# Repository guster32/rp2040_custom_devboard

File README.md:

https://datasheets.raspberrypi.com/rp2040/rp2040-datasheet.pdf

https://cdn.sparkfun.com/assets/5/d/3/1/f/hardware-design-with-rp2040.pdf

https://datasheets.raspberrypi.com/rp2040/MinimalKiCAD.zip

https://github.com/sethhillbrand/kicad_templates.git

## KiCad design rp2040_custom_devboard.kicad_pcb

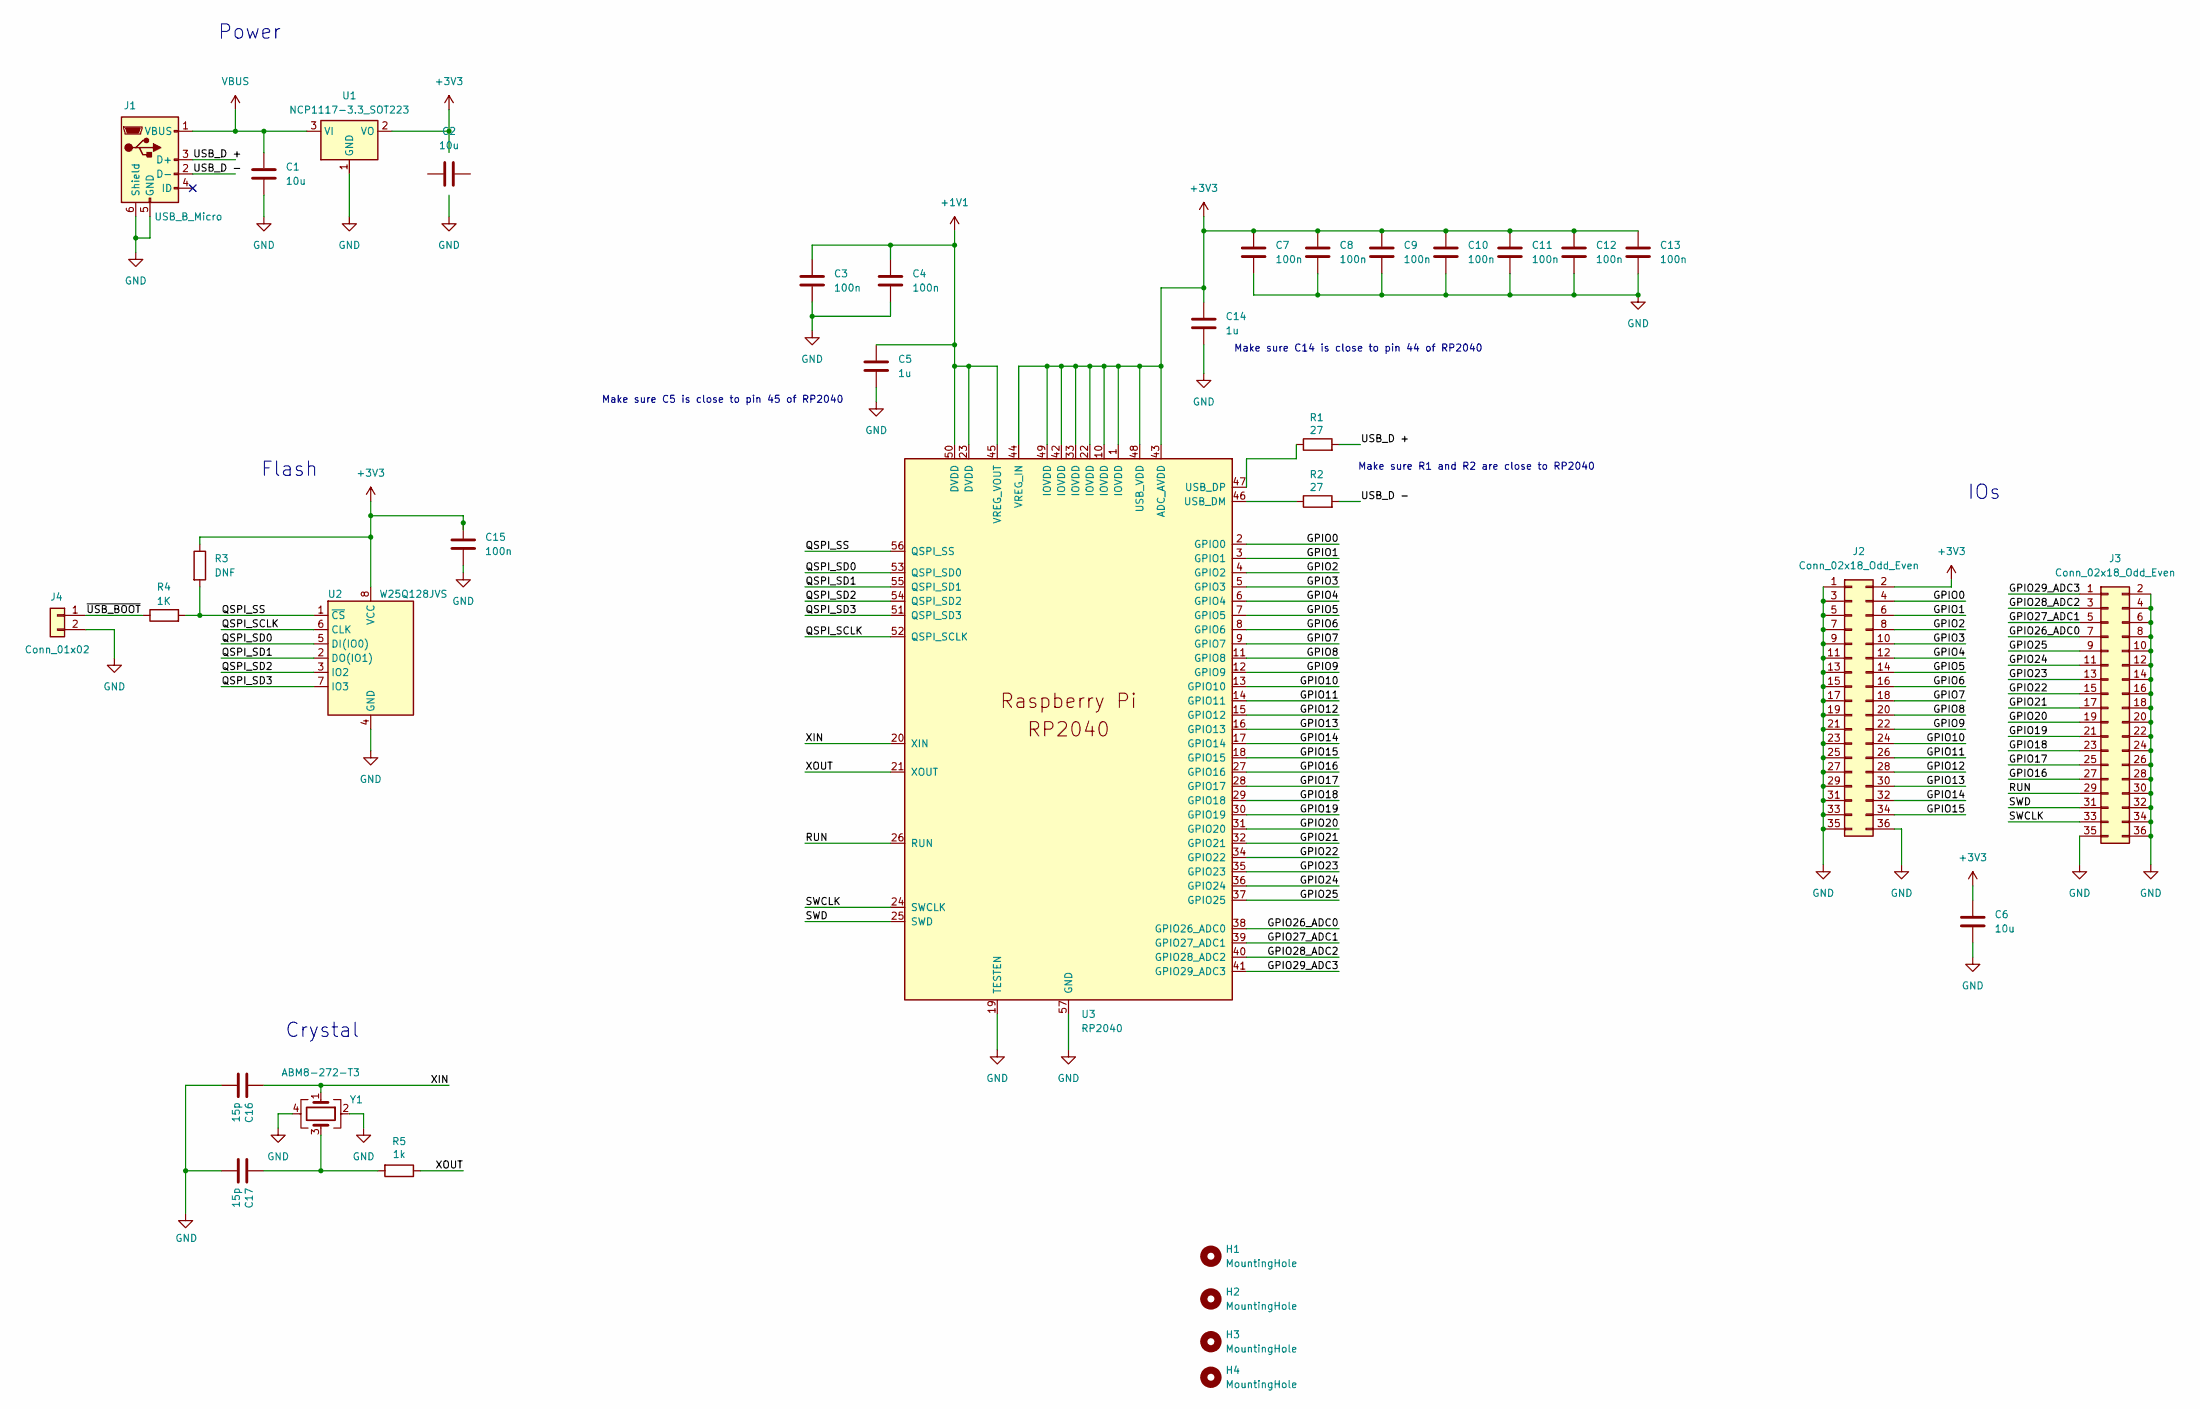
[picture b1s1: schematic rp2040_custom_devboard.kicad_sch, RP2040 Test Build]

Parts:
C1, C2, C6: 10u; C_0805_2012Metric
C3, C4, C7, C8, C9, C10, C11, C12, C13, C15: 100n; C_0402_1005Metric
C5, C14: 1u; C_0402_1005Metric
C16, C17: 15p; C_0402_1005Metric
H1, H2, H3, H4: MountingHole; MountingHole_2.7mm_M2.5
J1: USB_B_Micro; USB_Micro-B_Amphenol_10103594-0001LF_Horizontal
J2, J3: Conn_02x18_Odd_Even; PinHeader_2x18_P2.54mm_Vertical
J4: Conn_01x02; PinHeader_1x02_P2.54mm_Vertical
R1, R2: 27; R_0402_1005Metric
R3: DNF; R_0402_1005Metric
R4: 1K; R_0402_1005Metric
R5: 1k; R_0402_1005Metric
U1: NCP1117-3.3_SOT223; SOT-223-3_TabPin2
U2: W25Q128JVS; SOIC-8_5.23x5.23mm_P1.27mm
U3: RP2040; RP2040-QFN-56
Y1: ABM8-272-T3; Crystal_SMD_3225-4Pin_3.2x2.5mm

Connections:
+1V1: C3.1, C4.1, C5.1, U3.23 (DVDD), U3.45 (VREG_VOUT), U3.50 (DVDD)
+3V3: C6.1, C7.1, C8.1, C9.1, C10.1, C11.1, C12.1, C13.1, C14.1, C15.1, J2.2, R3.1, U1.2 (VO), U2.8 (VCC), U3.1 (IOVDD), U3.10 (IOVDD), U3.22 (IOVDD), U3.33 (IOVDD), U3.42 (IOVDD), U3.43 (ADC_AVDD), U3.44 (VREG_IN), U3.48 (USB_VDD), U3.49 (IOVDD)
/GPIO0: J2.4, U3.2 (GPIO0)
/GPIO1: J2.6, U3.3 (GPIO1)
/GPIO2: J2.8, U3.4 (GPIO2)
/GPIO3: J2.10, U3.5 (GPIO3)
/GPIO4: J2.12, U3.6 (GPIO4)
/GPIO5: J2.14, U3.7 (GPIO5)
/GPIO6: J2.16, U3.8 (GPIO6)
/GPIO7: J2.18, U3.9 (GPIO7)
/GPIO8: J2.20, U3.11 (GPIO8)
/GPIO9: J2.22, U3.12 (GPIO9)
/GPIO10: J2.24, U3.13 (GPIO10)
/GPIO11: J2.26, U3.14 (GPIO11)
/GPIO12: J2.28, U3.15 (GPIO12)
/GPIO13: J2.30, U3.16 (GPIO13)
/GPIO14: J2.32, U3.17 (GPIO14)
/GPIO15: J2.34, U3.18 (GPIO15)
/GPIO16: J3.27, U3.27 (GPIO16)
/GPIO17: J3.25, U3.28 (GPIO17)
/GPIO18: J3.23, U3.29 (GPIO18)
/GPIO19: J3.21, U3.30 (GPIO19)
/GPIO20: J3.19, U3.31 (GPIO20)
/GPIO21: J3.17, U3.32 (GPIO21)
/GPIO22: J3.15, U3.34 (GPIO22)
/GPIO23: J3.13, U3.35 (GPIO23)
/GPIO24: J3.11, U3.36 (GPIO24)
/GPIO25: J3.9, U3.37 (GPIO25)
/GPIO26_ADC0: J3.7, U3.38 (GPIO26_ADC0)
/GPIO27_ADC1: J3.5, U3.39 (GPIO27_ADC1)
/GPIO28_ADC2: J3.3, U3.40 (GPIO28_ADC2)
/GPIO29_ADC3: J3.1, U3.41 (GPIO29_ADC3)
/QSPI_SCLK: U2.6 (CLK), U3.52 (QSPI_SCLK)
/QSPI_SD0: U2.5 (DI(IO0)), U3.53 (QSPI_SD0)
/QSPI_SD1: U2.2 (DO(IO1)), U3.55 (QSPI_SD1)
/QSPI_SD2: U2.3 (IO2), U3.54 (QSPI_SD2)
/QSPI_SD3: U2.7 (IO3), U3.51 (QSPI_SD3)
/QSPI_SS: R3.2, R4.2, U2.1 (~CS), U3.56 (QSPI_SS)
/RUN: J3.29, U3.26 (RUN)
/SWCLK: J3.33, U3.24 (SWCLK)
/SWD: J3.31, U3.25 (SWD)
/USB_D +: J1.3 (D+), R1.2
/USB_D -: J1.2 (D-), R2.2
/XIN: C16.1, U3.20 (XIN), Y1.1
/XOUT: R5.1, U3.21 (XOUT)
/~USB_BOOT: J4.1, R4.1
GND: C1.2, C3.2, C4.2, C5.2, C6.2, C7.2, C8.2, C9.2, C10.2, C11.2, C12.2, C13.2, C14.2, C15.2, C16.2, C17.2, J1.5 (GND), J1.6 (Shield), J2.1, J2.3, J2.5, J2.7, J2.9, J2.11, J2.13, J2.15, J2.17, J2.19, J2.21, J2.23, J2.25, J2.27, J2.29, J2.31, J2.33, J2.35, J2.36, J3.2, J3.4, J3.6, J3.8, J3.10, J3.12, J3.14, J3.16, J3.18, J3.20, J3.22, J3.24, J3.26, J3.28, J3.30, J3.32, J3.34, J3.35, J3.36, J4.2, U1.1 (GND), U2.4 (GND), U3.19 (TESTEN), U3.57 (GND), Y1.2, Y1.4
unnamed: C17.1, R5.2, Y1.3
unnamed: R2.1, U3.46 (USB_DM)
unnamed: R1.1, U3.47 (USB_DP)
VBUS: C1.1, J1.1 (VBUS), U1.3 (VI)

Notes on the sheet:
Power
IOs
Make sure C14 is close to pin 44 of RP2040
Crystal
Make sure R1 and R2 are close to RP2040
Make sure C5 is close to pin 45 of RP2040
Flash

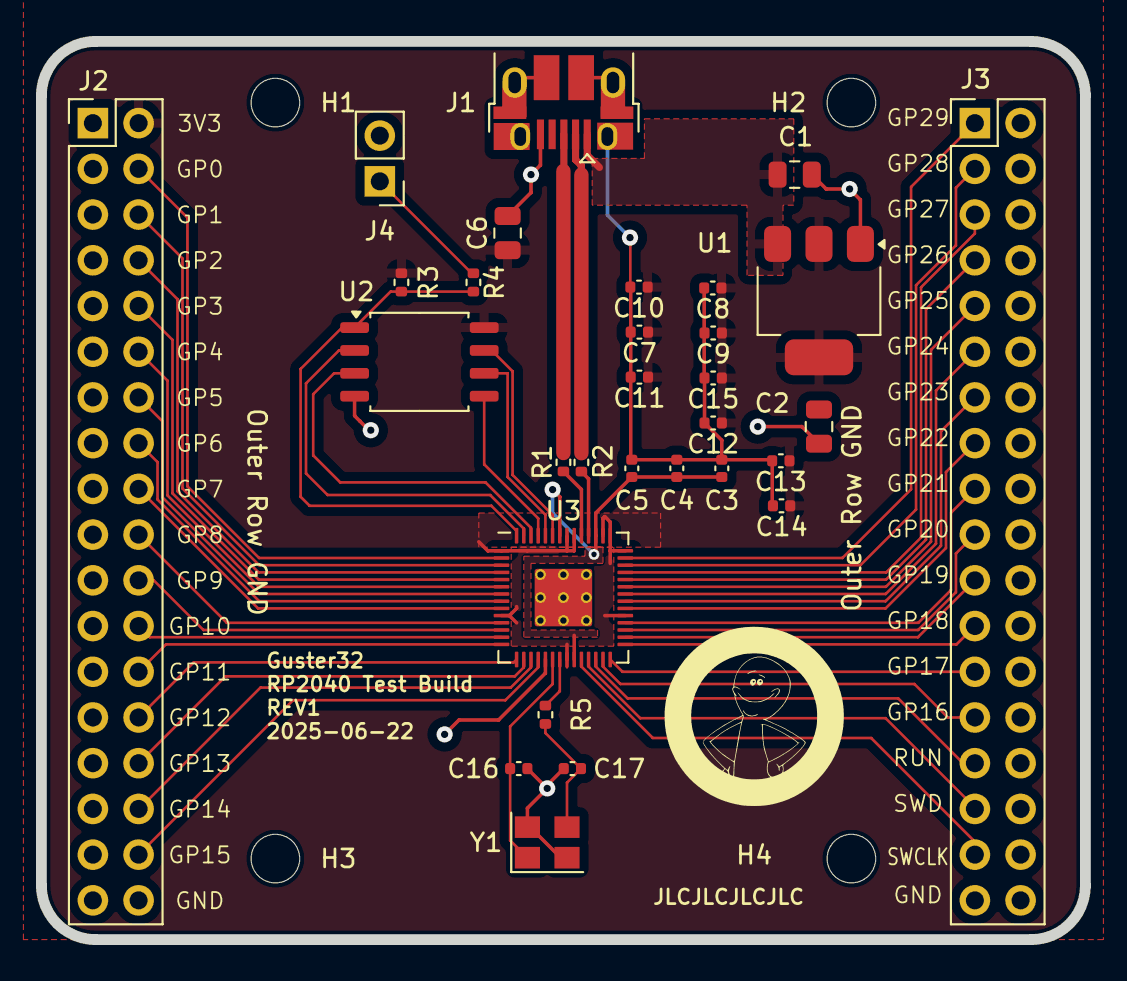
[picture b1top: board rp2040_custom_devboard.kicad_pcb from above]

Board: 4 copper layers, 58.0 x 49.9 mm, 34 parts (0 on the bottom side), 51 nets.

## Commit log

2025-06-24 Initial setup
2025-06-28 REV1
